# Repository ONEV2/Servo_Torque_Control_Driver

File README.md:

The version 1.1 uses attiny blue board for the controller rather than having a on-board SOC. 

The driver board acts as a shield for the blue board to be attached and detached on the go.

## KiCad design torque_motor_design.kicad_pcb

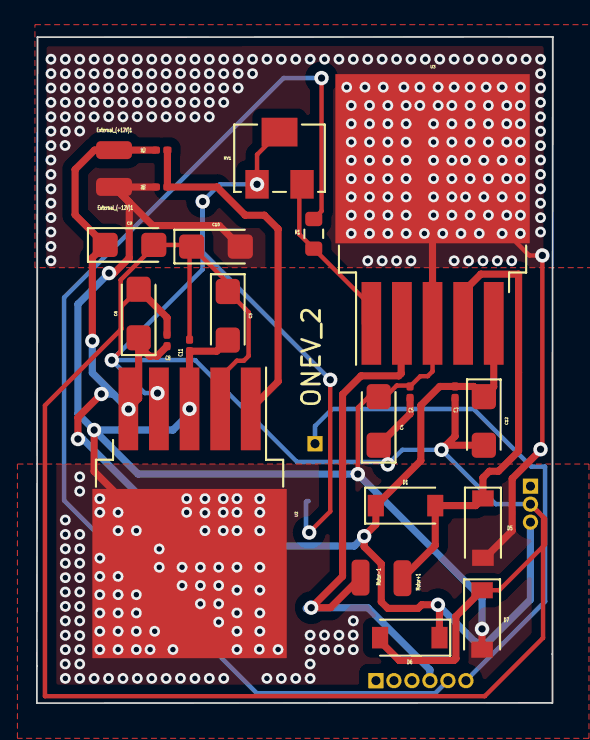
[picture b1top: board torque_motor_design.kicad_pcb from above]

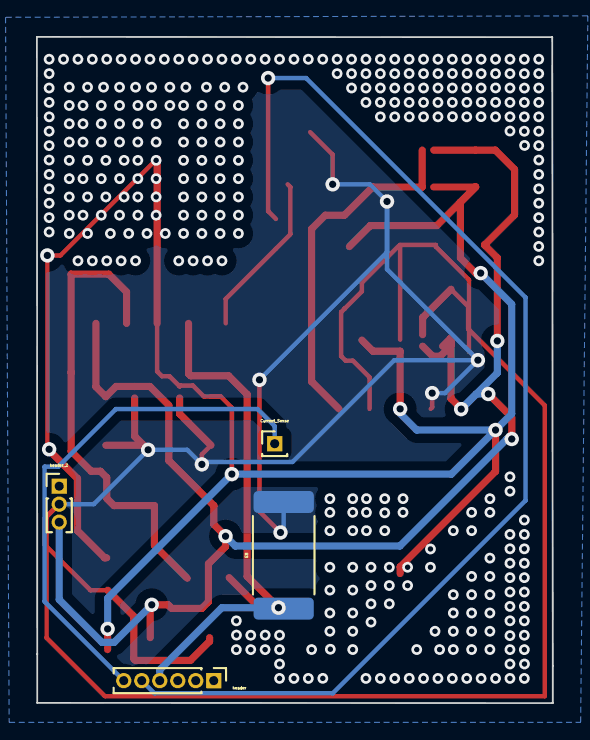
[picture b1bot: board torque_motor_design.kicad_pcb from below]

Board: 2 copper layers, 28.7 x 37.0 mm, 28 parts (4 on the bottom side), 9 nets.

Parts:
C3, C4, C6, C9, C10, C12: 10uF; CP_EIA-3216-18_Kemet-A
C5, C7, C8, C11: 0.1uF; C_0201_0603Metric
Current_Sense: PinHeader_1x01_P1.00mm_Vertical
D1, D5: D_Schottky; D_SOD-123
D6, D7: D_Zener; D_SOD-123
External_(+12V)1: Conn_01x01; SolderWirePad_1x01_SMD_1x2mm
External_(-12V)1: Conn_01x01; SolderWirePad_1x01_SMD_1x2mm
Motor+1: Conn_01x01; SolderWirePad_1x01_SMD_1x2mm
Motor-1: Conn_01x01; SolderWirePad_1x01_SMD_1x2mm
R1: 49k; R_0603_1608Metric
R3: 0.1; R_2512_6332Metric
R5, R6: 100k; R_0201_0603Metric
RV1: 1k; Potentiometer_Bourns_3224W_Vertical
U2, U3: OPAMP; TO-263-5_TabPin6
header: PinHeader_1x06_P1.00mm_Vertical
header_2: PinHeader_1x03_P1.00mm_Vertical

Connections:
+V: C6.1, C7.1, C8.1, C9.1, C12.1, D1.1 (K), D6.1 (K), External_(+12V)1.1, R5.1, U2.5 (V-), U3.5 (V-), header_2.3
-V: C3.2, C4.2, C5.1, C10.2, C11.1, D5.2 (A), D7.2 (A), External_(-12V)1.1, R6.2, U2.3, U2.6, U3.3, U3.6
GND: C3.1, C4.1, C5.2, C6.2, C7.2, C8.2, C9.2, C10.1, C11.2, C12.2, D6.2 (A), D7.1 (K), R3.2, RV1.1, RV1.2, U2.2 (-), U2.4 (V+), header_2.2
unnamed: D1.2 (A), D5.1 (K), Motor+1.1, U3.4 (V+)
unnamed: Motor-1.1, R3.1, U3.2 (-), header.4
unnamed: R1.2, RV1.3, U3.1 (+)
unnamed: R5.2, R6.1, U2.1 (+)
Torque_Mode: R1.1, header.5
current_sense: Current_Sense.1, header.6

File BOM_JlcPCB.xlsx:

Comment | Designator | Footprint | JLCPCB Part #（optional）
0.1uF | C8,C7,C5,C11 | C_0201_0603Metric | C30926
10uF | C6,C10,C9,C4,C12,C3 | CP_EIA-3216-18_Kemet-A | C128254
1k | RV1 | Potentiometer_Bourns_3224W_Vertical | C50204
100k | R6,R5 | R_0201_0603Metric | C365065
OPAMP | U3,U2 | TO-263-5_TabPin6 | C527495
D_zener | D7,D6 | D_SOD-123 | C364306
D_Schottky | D1,D5 | D_SOD-123 | C8598
49k | R1 | R_0603_1608Metric | C365177
0.1 | R3 | R_2512_6332Metric | C154690

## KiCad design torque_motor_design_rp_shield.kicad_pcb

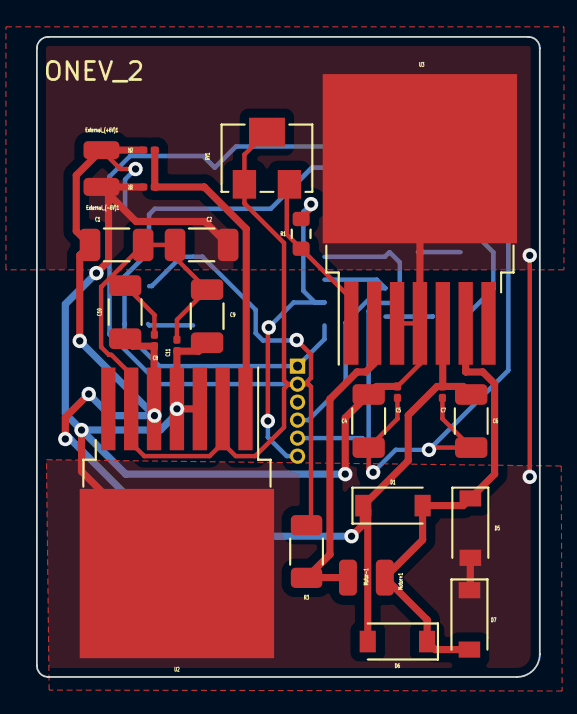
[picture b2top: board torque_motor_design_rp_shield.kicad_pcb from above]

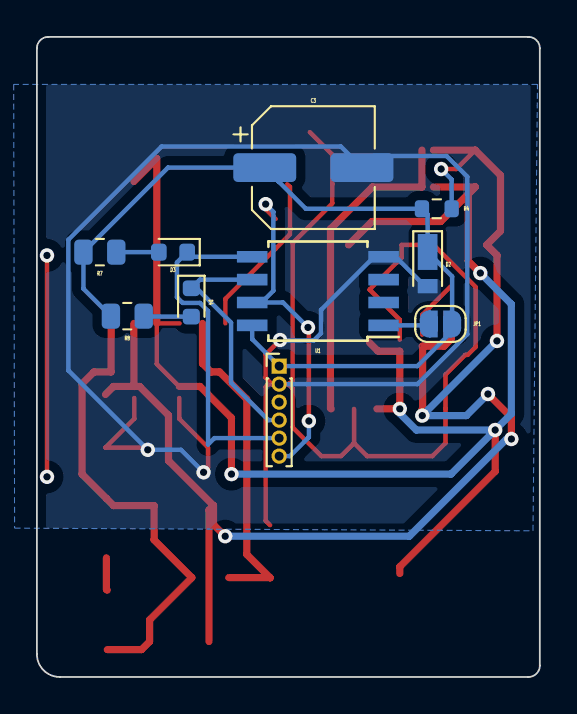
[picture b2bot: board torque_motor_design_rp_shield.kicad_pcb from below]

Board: 2 copper layers, 27.9 x 35.6 mm, 35 parts (10 on the bottom side), 14 nets.

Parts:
C1, C2, C4, C6, C9, C10: 10uF; C_1206_3216Metric
C3: 100uF; CP_Elec_6.3x5.7
C5, C7, C8, C11: 0.1uF; C_0201_0603Metric
D1, D5: D_Schottky; D_SOD-123
D2: zener; D_TUMD2
D3, D4: LED; LED_0603_1608Metric
D6, D7: D_Zener; D_SOD-123
External_(+6V)1: Conn_01x01; SolderWirePad_1x01_SMD_1x2mm
External_(-6V)1: Conn_01x01; SolderWirePad_1x01_SMD_1x2mm
JP1: Jumper_2_Open; SolderJumper-2_P1.3mm_Open_RoundedPad1.0x1.5mm
Motor+1: Conn_01x01; SolderWirePad_1x01_SMD_1x2mm
Motor-1: Conn_01x01; SolderWirePad_1x01_SMD_1x2mm
ONEV_2: PinHeader_1x06_P1.00mm_Vertical
R1: 100k; R_0603_1608Metric
R3: 0.1; R_1206_3216Metric
R4: 150; R_0603_1608Metric
R5, R6: 100k; R_0201_0603Metric
R7, R8: 220; R_0805_2012Metric
RV1: 1k; Potentiometer_Bourns_3214W_Vertical
U1: ATtiny85-20S; SOIC-8W_5.3x5.3mm_P1.27mm
U2, U3: OPAMP; TO-263-7_TabPin8

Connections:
+V: C1.1, C6.1, C7.1, C8.1, C10.1, D1.1 (K), D6.2 (A), External_(+6V)1.1, R4.1, R5.1, U2.5 (V-), U3.5 (V-)
-V: C2.2, C4.1, C5.1, C9.1, C11.1, D5.2 (A), D7.1 (K), External_(-6V)1.1, R6.2, U2.3, U2.4 (V+), U2.8, U3.3, U3.4 (V+), U3.8
GND: C1.2, C2.1, C3.2, C4.2, C5.2, C6.2, C7.2, C8.2, C9.2, C10.2, C11.2, D2.2 (A), ONEV_2.2, R3.2, RV1.1, RV1.2, U1.4 (GND), U2.2 (-), U2.6
unnamed: D3.2 (A), R7.2
unnamed: D4.2 (A), R8.1
unnamed: Motor-1.1, R3.1, U3.2 (-)
unnamed: R1.2, RV1.3, U3.1 (+)
unnamed: R5.2, R6.1, U2.1 (+)
unnamed: JP1.1 (A), U1.1 (~RESET/PB5)
unnamed: D1.2 (A), D5.1 (K), D6.1 (K), D7.2 (A), Motor+1.1, U3.6
RX_Serial: D4.1 (K), ONEV_2.4, U1.6 (PB1)
TX_Serial: D3.1 (K), ONEV_2.5, U1.5 (AREF/PB0)
Torque_Mode: ONEV_2.6, R1.1, U1.7 (PB2)
VCC_MCU_5V: C3.1, D2.1 (K), JP1.2 (B), ONEV_2.1, R4.2, R7.1, R8.2, U1.8 (VCC)

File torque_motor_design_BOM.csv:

"Id";"Designator";"Package";"Quantity";"Designation";"Supplier and ref";
1;"C8,C7,C5,C11";"C_0201_0603Metric";4;"0.1uF";;;
2;"C6,C10,C9,C4,C12,C3,C2,C1";"CP_EIA-3216-18_Kemet-A";8;"10uF";;;
3;"RV1";"Potentiometer_Bourns_3214W_Vertical";1;"1k";;;
4;"R6,R5";"R_0201_0603Metric";2;"100k";;;
5;"U3,U2";"TO-263-7_TabPin8";2;"OPAMP";;;
6;"Motor+1,External_(-6V)1,External_(+6V)1,Motor-1";"SolderWirePad_1x01_SMD_1x2mm";4;"Conn_01x01";;;
7;"D7,D6";"D_SOD-123";2;"D_Zener";;;
8;"D1,D5";"D_SOD-123";2;"D_Schottky";;;
9;"R1";"R_0603_1608Metric";1;"100k";;;
10;"Enable_Current_sense,JP1,Torque_mode_EN";"SolderJumper-2_P1.3mm_Open_RoundedPad1.0x1.5mm";3;"Jumper_2_Open";;;
11;"Current_Sense";"PinHeader_1x01_P1.00mm_Vertical";1;"PinHeader_1x01_P1.00mm_Vertical";;;
12;"U4";"SOT-89-3";1;"L78L05_SO8";;;
13;"U1";"SOIC-8W_5.3x5.3mm_P1.27mm";1;"ATtiny85-20S";;;
14;"R8,R7";"R_0805_2012Metric";2;"220";;;
15;"D4,D3";"LED_0603_1608Metric";2;"LED";;;
16;"ONEV_2";"PinHeader_1x06_P1.00mm_Vertical";1;"PinHeader_1x06_P1.00mm_Vertical";;;
17;"R3";"R_2512_6332Metric";1;"0.1";;;

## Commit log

2022-07-13 Add: kicad files
2022-07-13 Add: Images for Readme
2022-07-13 Add:Version_1
2022-07-18 Add:v1.1
2022-07-19 Add:Production Files
2022-07-20 Update: BOM files
2022-07-20 Add: Production Files
